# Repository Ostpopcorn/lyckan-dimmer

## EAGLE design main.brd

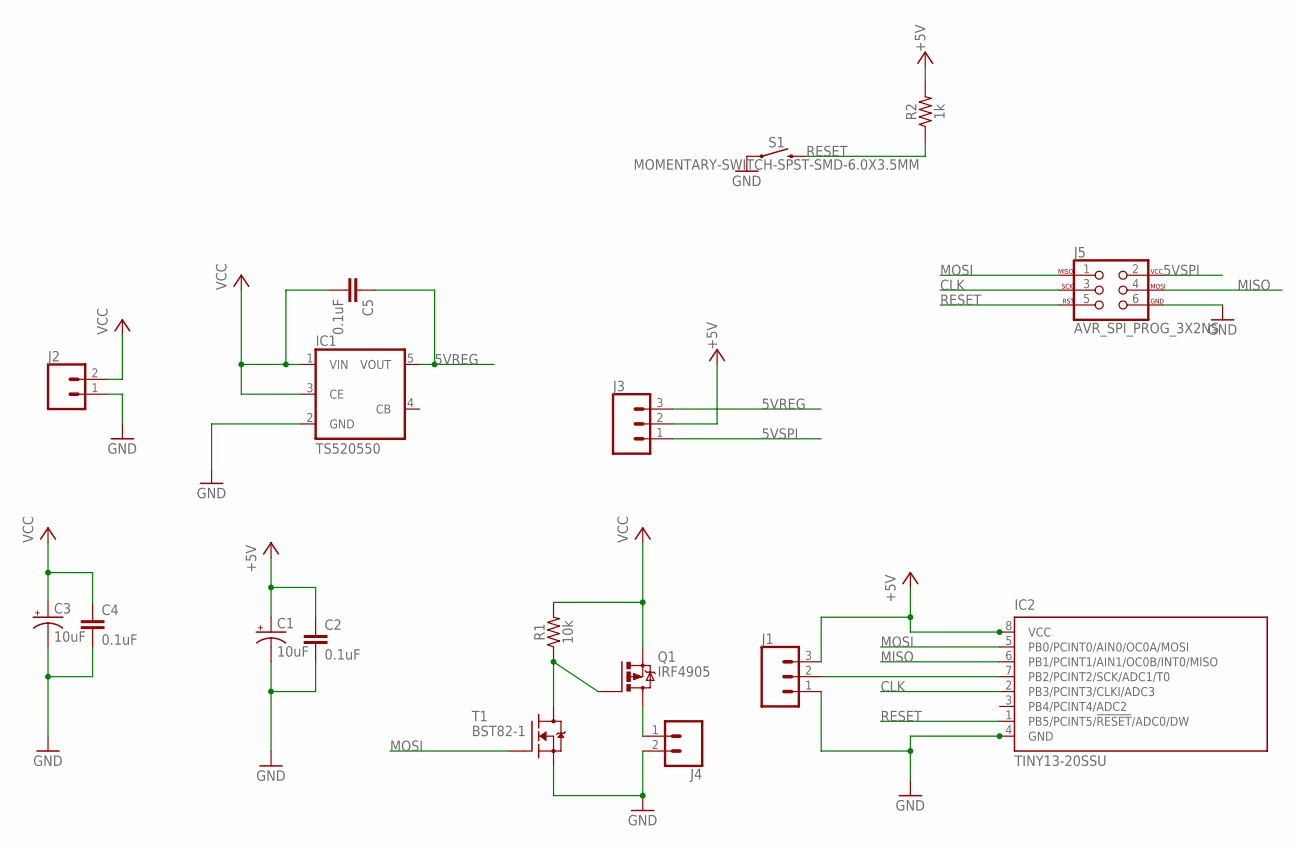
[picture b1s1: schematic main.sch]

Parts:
C1, C3: 10uF; CPOL-RADIAL-2.5MM-5MM
C2, C4, C5: 0.1uF; 0603
IC1: TS520550; SOT25
IC2: TINY13-20SSU; 8S1
J1, J3: CONN_03; 1X03
J2: CONN_023.5MM_LOCK; SCREWTERMINAL-3.5MM-2_LOCK
J4: CONN_023.5MM; SCREWTERMINAL-3.5MM-2
J5: AVR_SPI_PROG_3X2NS; 2X3-NS
Q1: IRF4905; TO220BH
R1: 10k; 0603
R2: 1k; 0603
S1: MOMENTARY-SWITCH-SPST-SMD-6.0X3.5MM; TACTILE_SWITCH_SMD_6.0X3.5MM
T1: BST82-1; SOT23

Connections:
5VREG: C5.1, IC1.5 (VOUT), J3.3
5VSPI: J3.1, J5.2
+5V: C1.1 (+), C2.1, IC2.8 (VCC), J1.3, J3.2, R2.2
CLK: IC2.2 (PB3/PCINT3/CLKI/ADC3), J5.3
GND: C1.2 (-), C2.2, C3.2 (-), C4.2, IC1.2 (GND), IC2.4 (GND), J1.1, J2.1, J4.2, J5.6, S1.1, T1.2 (S)
MISO: IC2.6 (PB1/PCINT1/AIN1/OC0B/INT0/MISO), J5.4
MOSI: IC2.5 (PB0/PCINT0/AIN0/OC0A/MOSI), J5.1, T1.1 (G)
unnamed: J4.1, Q1.D
unnamed: IC2.7 (PB2/PCINT2/SCK/ADC1/T0), J1.2
unnamed: Q1.G, R1.1, T1.3 (D)
RESET: IC2.1 (PB5/PCINT5/!RESET!/ADC0/DW), J5.5, R2.1, S1.2
VCC: C3.1 (+), C4.1, C5.2, IC1.1 (VIN), IC1.3 (CE), J2.2, Q1.S, R1.2

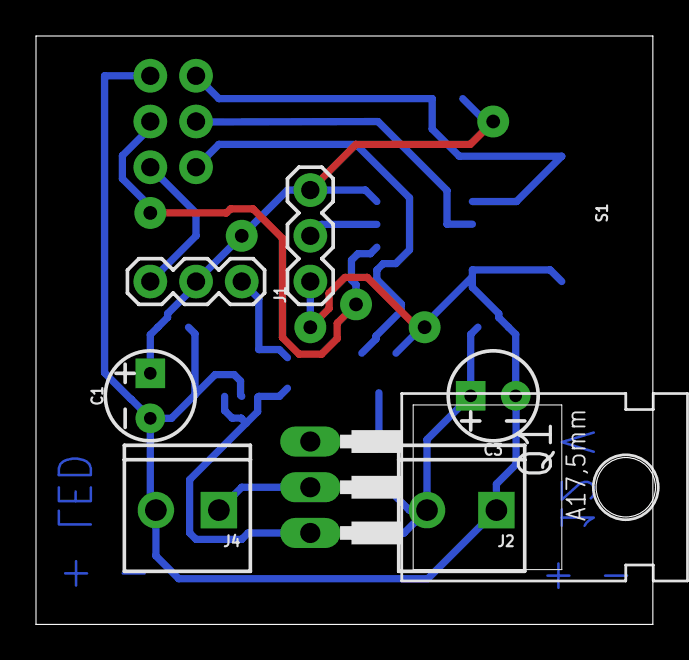
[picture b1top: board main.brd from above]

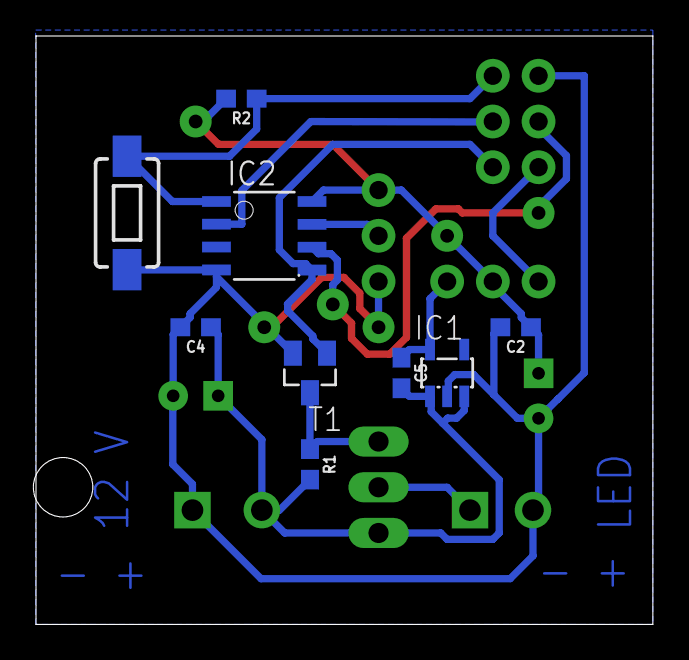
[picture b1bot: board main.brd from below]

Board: 2 copper layers, 34.3 x 32.7 mm, 17 parts (9 on the bottom side), 12 nets.

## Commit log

2020-01-07 Added first pcb. To weak mosfet and no led indicator.
2020-01-10 Larger MOSFET, smaller SPI header and a rearrange.

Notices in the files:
parts and their libraries:
SparkFun-Connectors: Licensing: Creative Commons ShareAlike 4.0 International - https://creativecommons.org/licenses/by-sa/4.0
